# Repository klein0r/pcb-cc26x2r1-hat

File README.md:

# CC26X2R1 Hat

Just a simple hat to connect a [USR-TCP232-T2](https://haus-auto.com/p/ali/TCPSerialAdapter) TTL to the [CC26X2R1](https://www.ti.com/tool/LAUNCHXL-CC26X2R1)

[Gerber-Files](https://github.com/klein0r/pcb-cc26x2r1-hat/releases)

## Preview

## Parts

- U1: [USR-TCP232-T2](https://haus-auto.com/p/ali/TCPSerialAdapter)
- U2: Texas Instruments CC26X2R1

## License

The MIT License (MIT)

Copyright (c) 2026 Matthias Kleine <info@haus-automatisierung.com>

Permission is hereby granted, free of charge, to any person obtaining a copy
of this software and associated documentation files (the "Software"), to deal
in the Software without restriction, including without limitation the rights
to use, copy, modify, merge, publish, distribute, sublicense, and/or sell
copies of the Software, and to permit persons to whom the Software is
furnished to do so, subject to the following conditions:

The above copyright notice and this permission notice shall be included in
all copies or substantial portions of the Software.

THE SOFTWARE IS PROVIDED "AS IS", WITHOUT WARRANTY OF ANY KIND, EXPRESS OR
IMPLIED, INCLUDING BUT NOT LIMITED TO THE WARRANTIES OF MERCHANTABILITY,
FITNESS FOR A PARTICULAR PURPOSE AND NONINFRINGEMENT. IN NO EVENT SHALL THE
AUTHORS OR COPYRIGHT HOLDERS BE LIABLE FOR ANY CLAIM, DAMAGES OR OTHER
LIABILITY, WHETHER IN AN ACTION OF CONTRACT, TORT OR OTHERWISE, ARISING FROM,
OUT OF OR IN CONNECTION WITH THE SOFTWARE OR THE USE OR OTHER DEALINGS IN
THE SOFTWARE.

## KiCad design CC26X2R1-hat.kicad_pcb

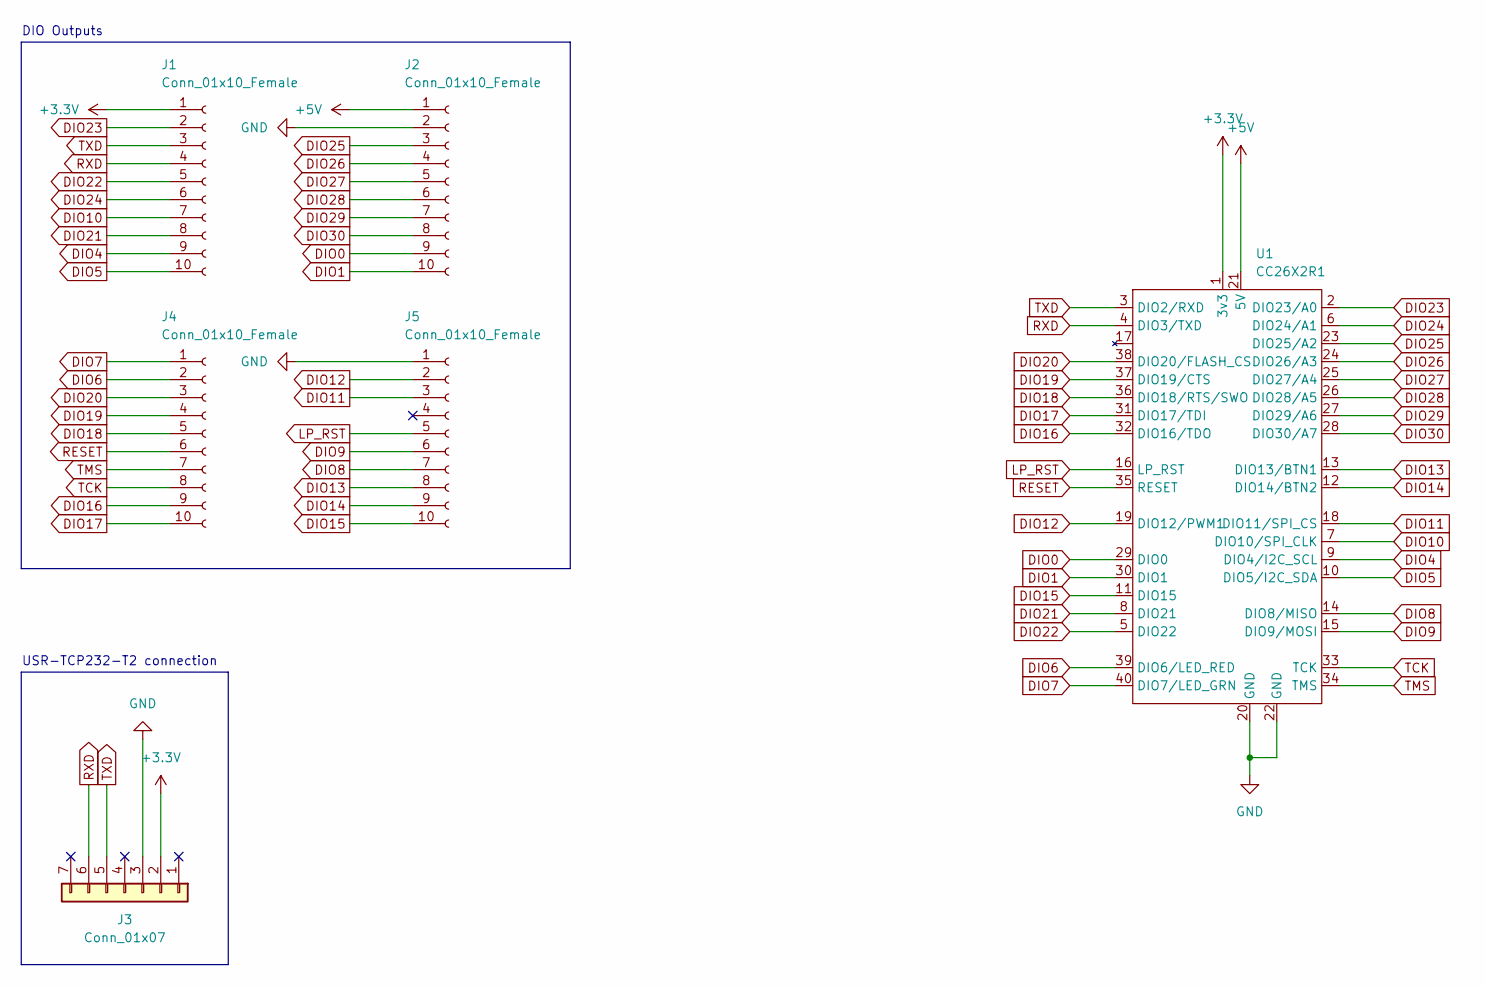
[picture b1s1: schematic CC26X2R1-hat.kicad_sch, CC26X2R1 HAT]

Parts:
J1, J2, J4, J5: Conn_01x10_Female; PinHeader_1x10_P2.54mm_Vertical
J3: Conn_01x07; PinHeader_1x07_P2.54mm_Vertical
U1: CC26X2R1

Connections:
+3V3: J1.1, J3.2, U1.1 (3v3)
+5V: J2.1, U1.21 (5V)
DIO0: J2.9, U1.29 (DIO0)
DIO1: J2.10, U1.30 (DIO1)
DIO4: J1.9, U1.9 (DIO4/I2C_SCL)
DIO5: J1.10, U1.10 (DIO5/I2C_SDA)
DIO6: J4.2, U1.39 (DIO6/LED_RED)
DIO7: J4.1, U1.40 (DIO7/LED_GRN)
DIO8: J5.7, U1.14 (DIO8/MISO)
DIO9: J5.6, U1.15 (DIO9/MOSI)
DIO10: J1.7, U1.7 (DIO10/SPI_CLK)
DIO11: J5.3, U1.18 (DIO11/SPI_CS)
DIO12: J5.2, U1.19 (DIO12/PWM1)
DIO13: J5.8, U1.13 (DIO13/BTN1)
DIO14: J5.9, U1.12 (DIO14/BTN2)
DIO15: J5.10, U1.11 (DIO15)
DIO16: J4.9, U1.32 (DIO16/TDO)
DIO17: J4.10, U1.31 (DIO17/TDI)
DIO18: J4.5, U1.36 (DIO18/RTS/SWO)
DIO19: J4.4, U1.37 (DIO19/CTS)
DIO20: J4.3, U1.38 (DIO20/FLASH_CS)
DIO21: J1.8, U1.8 (DIO21)
DIO22: J1.5, U1.5 (DIO22)
DIO23: J1.2, U1.2 (DIO23/A0)
DIO24: J1.6, U1.6 (DIO24/A1)
DIO25: J2.3, U1.23 (DIO25/A2)
DIO26: J2.4, U1.24 (DIO26/A3)
DIO27: J2.5, U1.25 (DIO27/A4)
DIO28: J2.6, U1.26 (DIO28/A5)
DIO29: J2.7, U1.27 (DIO29/A6)
DIO30: J2.8, U1.28 (DIO30/A7)
GND: J2.2, J3.3, J5.1, U1.20 (GND), U1.22 (GND)
LP_RST: J5.5, U1.16 (LP_RST)
RESET: J4.6, U1.35 (RESET)
RXD: J1.4, J3.6, U1.4 (DIO3/TXD)
TCK: J4.8, U1.33 (TCK)
TMS: J4.7, U1.34 (TMS)
TXD: J1.3, J3.5, U1.3 (DIO2/RXD)

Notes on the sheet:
DIO Outputs
USR-TCP232-T2 connection

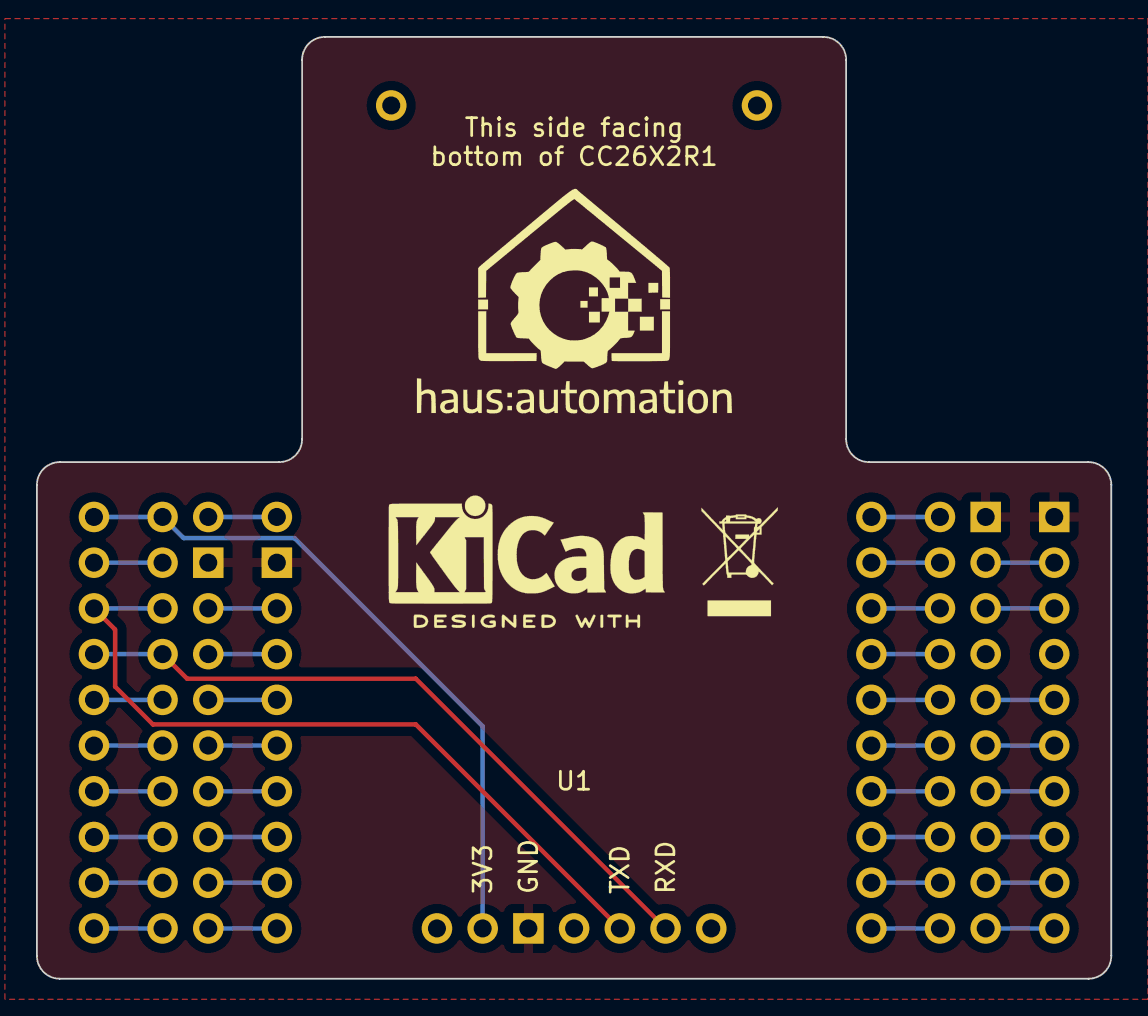
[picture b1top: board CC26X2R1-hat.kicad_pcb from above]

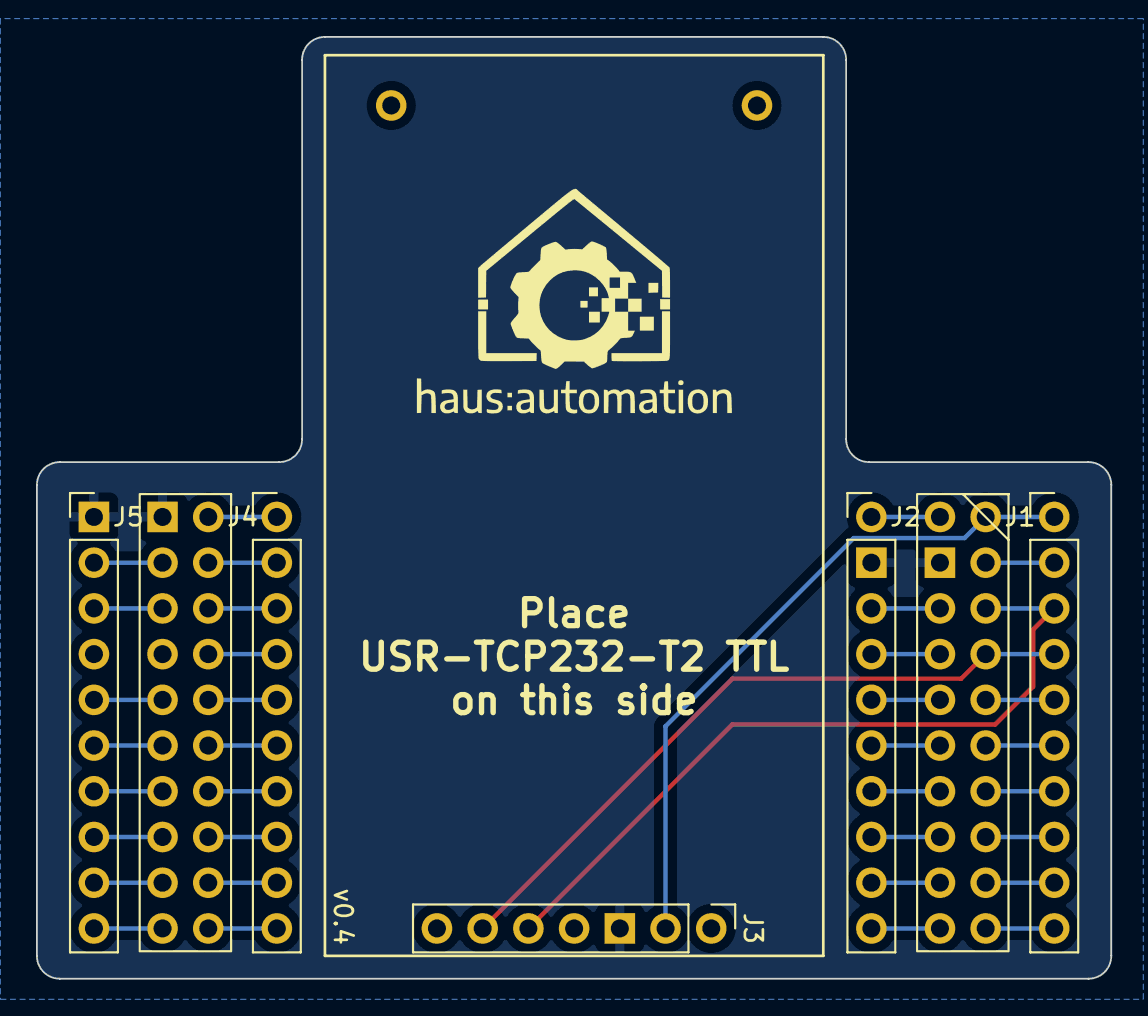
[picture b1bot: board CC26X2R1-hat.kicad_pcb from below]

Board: 2 copper layers, 59.7 x 52.3 mm, 6 parts (5 on the bottom side), 38 nets.

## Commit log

2022-01-30 Init
2022-01-30 v0.1
2022-01-30 Create LICENSE
2022-02-10 Added labels
2022-02-10 Added preview image
2022-02-10 Updated preview for 0.2
2024-03-15 v0.3
2024-04-30 v0.4
2026-01-28 Year 2026
